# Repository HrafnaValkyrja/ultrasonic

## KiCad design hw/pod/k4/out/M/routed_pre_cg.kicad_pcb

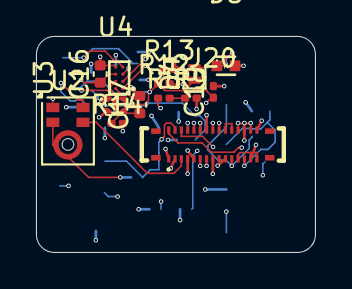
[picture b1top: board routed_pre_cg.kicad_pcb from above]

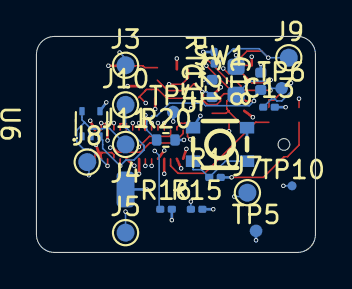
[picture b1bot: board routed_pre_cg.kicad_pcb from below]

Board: 6 copper layers, 15.5 x 12.0 mm, 37 parts (23 on the bottom side), 21 nets.

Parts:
C13, C19: C_0201_0603Metric
C15, C16, C17, C18: C_0402_1005Metric
C21: C_0603_1608Metric
D4: D_SOD-882
D5: X1SON-2_L1.0-W0.6-P0.65-BI-1
J3, J5, J7, J8, J9, J10, J11: TestPoint_Pad_D1.0mm
J4: WirePad_1.0x2.0mm
J20: CONN-SMD_BM28B0.6-30DS-2-0.35V-51; BM28B0.6-30DS_2-0.35V
R8, R9, R10, R12, R13, R14, R15, R16: R_0201_0603Metric
R20: R_0402_1005Metric
RT1: R_0201_0603Metric
SW1: SW-SMD_4P-L3.0-W2.6-P1.85-LS3.4
TP4, TP5, TP6: TestPoint_Pad_D0.7mm
TP10: TestDot_D0.5mm
U2: Knowles_LGA-5_3.5x2.65mm; Knowles_LGA-5_3.5x2.65mm_Port0.65
U3: DSBGA-8_L1.6-W0.9-R2-C4-P0.40-BL
U4: X2SON-4_L1.0-W1.0-P0.65-TL-EP
U6: SOT-553-5_L1.6-W1.2-P0.50-LS1.6-TL-1

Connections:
+3V0: J20.17, J20.18, J20.19, R15.2, R16.2, R20.2, SW1.1, SW1.2, TP4.1
BTN: J20.29, R10.1, SW1.3, SW1.4
CHG_INT: J20.26, U3.A1
DOCK_VBUS: D4.2, D5.1, J3.1
GND: C13.2, C15.2, C16.2, C17.2, C18.2, C19.2, C21.2, D5.2, J4.1, J20.1, J20.2, J20.4, J20.5, J20.8, J20.9, J20.10, J20.12, J20.14, J20.15, J20.16, J20.20, J20.21, J20.24, R9.2, R10.2, R13.2, RT1.2, TP5.1, U2.2, U2.3, U3.D2, U4.2, U4.5, U6.4
I2C_SCL: J20.23, R15.1, U3.B1
I2C_SDA: J20.25, R16.1, U3.C1
LDO_OUT: C18.1, R20.1, U4.1
LED_A: J7.1, R14.2
LED_K: J8.1, J20.30
MIC_CLK: J20.3, U2.4
MIC_DATA: J20.7, TP10.1, U2.1
MIC_VDD: C13.1, J20.6, U2.5
TS: J9.1, J20.22, RT1.1, U3.D1
USB_DM: J11.1, J20.13, U6.5
USB_DP: J10.1, J20.11, U6.3
VBAT: C16.1, J5.1, R8.1, U3.C2
VBAT_SENSE: C19.1, J20.28, R8.2, R9.1
VBUS: C15.1, D4.1, R12.1, U3.A2
VBUS_SENSE: J20.27, R12.2, R13.1
VSYS: C17.1, C21.1, R14.1, TP6.1, U3.B2, U4.3, U4.4

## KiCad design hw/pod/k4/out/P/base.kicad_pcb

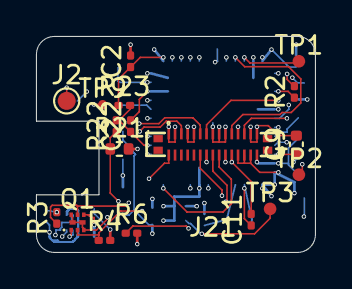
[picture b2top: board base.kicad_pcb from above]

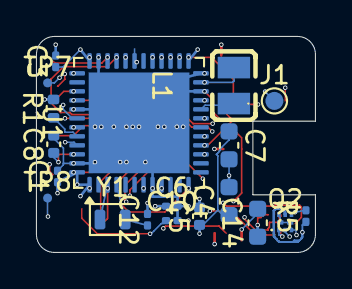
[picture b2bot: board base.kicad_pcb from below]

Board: 6 copper layers, 15.5 x 12.0 mm, 37 parts (19 on the bottom side), 35 nets.

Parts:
C1, C2, C3, C6, C10, C11, C12, C22: C_0201_0603Metric
C4, C7, C14: C_0603_1608Metric
C5, C8, C9: C_0402_1005Metric
J1, J2: TestPoint_Pad_D1.0mm
J21: CONN-SMD_BM28B0.6-30DP-2-0.35V-51; BM28B0.6-30DP_2-0.35V
L1: L0806
Q1, Q2: Nexperia_SOT1216_DFN1010B-6
R1, R21: R_0402_1005Metric
R2, R3, R4, R5, R6, R22, R23: R_0201_0603Metric
TP1, TP2, TP3: TestPoint_Pad_D0.7mm
TP7, TP8, TP9: TestDot_D0.5mm
U1: QFN-48-1EP_7x7mm_P0.5mm_EP5.6x5.6mm
Y1: Crystal_SMD_2012-2Pin_2.0x1.2mm

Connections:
+3V0: C1.1, C2.1, C3.1, C4.1, C5.1, C6.1, C7.1, C14.1, J21.17, J21.18, J21.19, Q1.4, Q2.4, R3.2, R5.2, R23.1, U1.1, U1.9, U1.21, U1.25, U1.36, U1.48
BRIDGE_RTN: Q1.1, Q2.1, R21.1, R22.1
BTN: J21.29, U1.10
CHG_INT: J21.27, U1.38
DBG_TX: TP7.1, U1.42
GA_N: Q1.2, R4.1, U1.17
GA_P: Q1.5, R3.1, U1.29
GB_N: Q2.2, R6.1, U1.28
GB_P: Q2.5, R5.1, U1.31
GND: C1.2, C2.2, C3.2, C4.2, C5.2, C6.2, C7.2, C8.2, C9.2, C10.2, C11.2, C12.2, C14.2, C22.2, J21.1, J21.2, J21.4, J21.5, J21.8, J21.9, J21.10, J21.12, J21.14, J21.15, J21.16, J21.20, J21.21, J21.24, R1.2, R4.2, R6.2, R21.2, U1.8, U1.22, U1.24, U1.35, U1.41, U1.47, U1.49
I2C_SCL: J21.23, U1.26
I2C_SDA: J21.25, U1.27
I_SENSE: C22.1, R22.2, R23.2, U1.16
LED_K: J21.30, U1.43
LSE_IN: C11.1, U1.3, Y1.1
LSE_OUT: C12.1, U1.4, Y1.2
MDF_CCK: TP8.1, U1.45
MDF_SDI: TP9.1, U1.19
MIC_CLK: J21.3, R2.2
MIC_DATA: J21.7, U1.40
MIC_VDD: J21.6, U1.15
unnamed: R1.1, U1.44
unnamed: R2.1, U1.39
NRST: C10.1, TP3.1, U1.7
OUT_A: J1.1, Q1.3, Q1.6, Q1.7, Q1.8
OUT_B: J2.1, Q2.3, Q2.6, Q2.7, Q2.8
SWCLK: TP2.1, U1.37
SWDIO: TP1.1, U1.34
TS: J21.22, U1.12
USB_DM: J21.13, U1.32
USB_DP: J21.11, U1.33
VBAT_SENSE: J21.28, U1.14
VBUS_SENSE: J21.26, U1.11
VDD11: C8.1, C9.1, L1.2, U1.23, U1.46
VLXSMPS: L1.1, U1.20
